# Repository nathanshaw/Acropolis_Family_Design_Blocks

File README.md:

# hsw_design_blocks
A collection of all the Hyper-Soundwalk EAGLE CAD design blocks.

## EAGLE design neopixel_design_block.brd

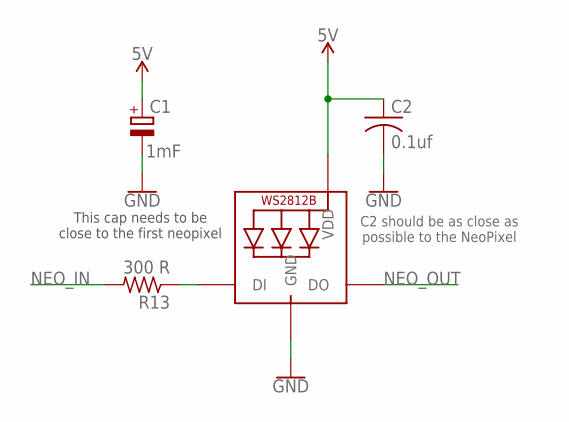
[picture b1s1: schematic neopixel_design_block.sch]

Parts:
C1: 1mF; 153CLV-1010
C2: 0.1uf; C0805K
NEO1: WS2812B5050; WS2812B
R13: 300 R; R0805

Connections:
5V: C1.+, C2.1, NEO1.1-VDD (VDD)
GND: C1.-, C2.2, NEO1.3-GND (GND)
NEO_IN: R13.2
NEO_OUT: NEO1.2-DOUT (DO)
NEO_P_CTRL_INT: NEO1.4-DIN (DI), R13.1

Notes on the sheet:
This cap needs to be close to the first neopixel
C2 should be as close as possible to the NeoPixel

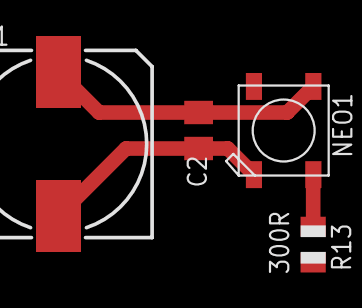
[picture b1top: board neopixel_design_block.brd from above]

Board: 2 copper layers, 4 parts (0 on the bottom side), 3 nets.

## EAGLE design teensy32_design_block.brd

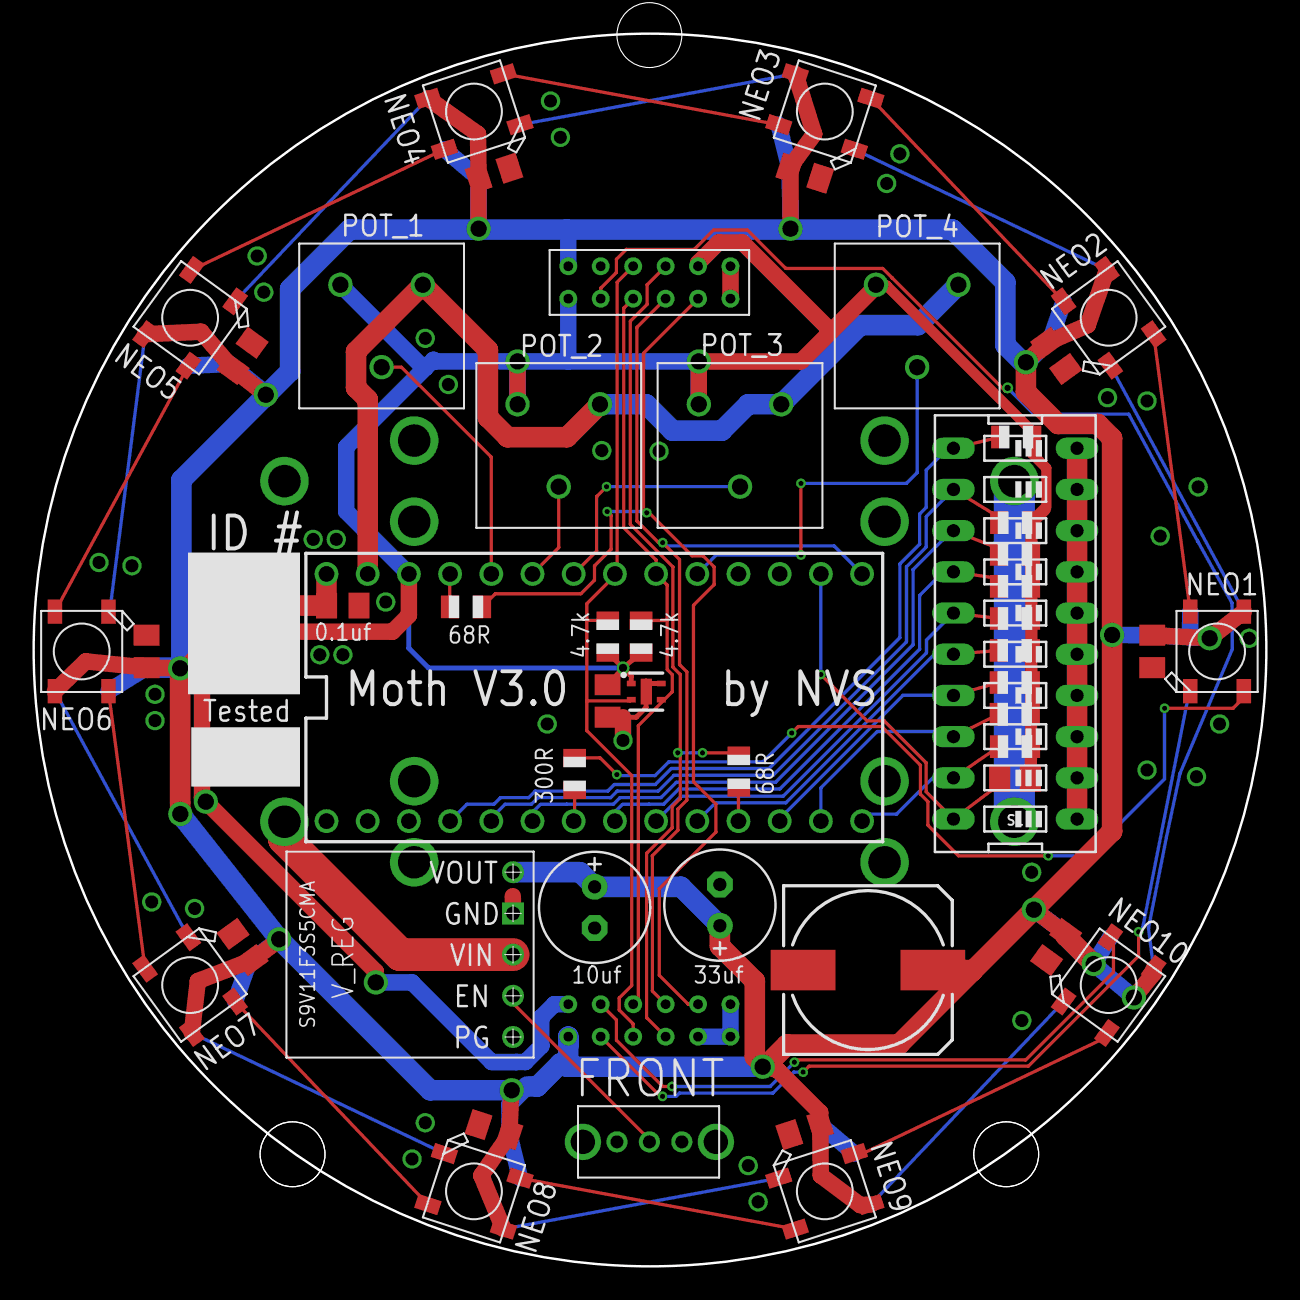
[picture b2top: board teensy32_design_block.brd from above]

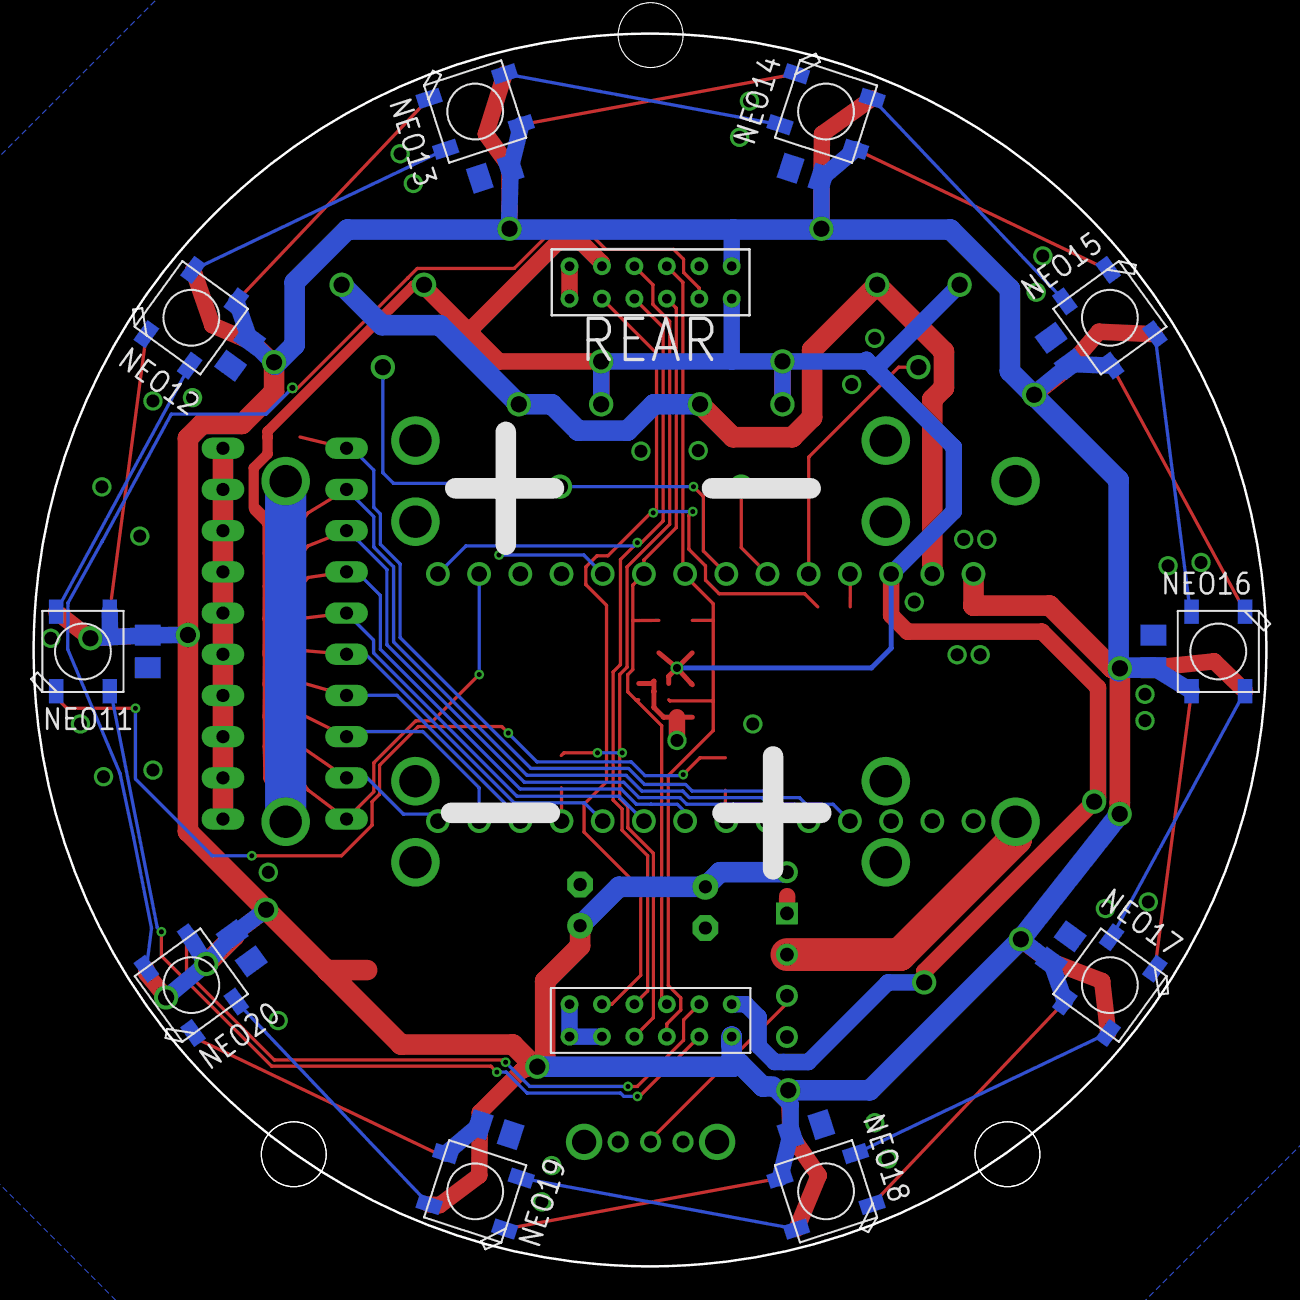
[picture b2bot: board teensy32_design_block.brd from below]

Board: 2 copper layers, 76.0 x 76.0 mm, 72 parts (22 on the bottom side), 51 nets.

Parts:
C10: 1mF; 153CLV-1010
FRONT: SAMTEC_ESQT_2X6_THROUGH_HOLE
NC1, NC2, NC3, NC4, NC5, NC6, NC7, NC8, NC9, NC10, NC11, NC12, NC13, NC14, NC15, NC16, NC17, NC18, NC19, NC20, NC21, NC24: 0.1uf; C0805K
NC22: 10uf; E2,5-7
NC23: 33uf; E2,5-7
NEO1, NEO2, NEO3, NEO4, NEO5, NEO6, NEO7, NEO8, NEO9, NEO10, NEO11, NEO12, NEO13, NEO14, NEO15, NEO16, NEO17, NEO18, NEO19, NEO20: WS2812B5050; WS2812B
POT1, POT2, POT3, POT4: 3386F_BOURNES_TRIM_POT; 3386_BOURNS_TRIM_POT
R1: 4.7k; R0805
R2: 4.7l; R0805
R3, R10: 68R; R0805
R13: 300 R; R0805
R14, R16, R17, R18, R19, R20, R21, R22, R24: 10k; R0805
R23: 10k; M0805
REAR: SAMTEC_ESQT_2X6_THROUGH_HOLE
S1: EDG-10
U1: SHTC3
U$1: 18500_CLIP_HOLDER; 3PINBATTERY_CLIP
U$2: OS_SPDT_SWITCH; OS_SPDT_SLIDE_SWITCH
U$3: TEENSY_3.1-3.2_DIL; TEENSY_3.0-3.2&LC_DIL
V_REG: S9V11F5S6CMA_NO_SEL; S9V11F3S5CMA_NO_SEL

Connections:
3.3V: FRONT.ESQT_6, NC24.1, POT1.P$2, POT2.P$2, POT3.P$2, POT4.P$2, R1.1, R2.1, R14.2, R16.2, R17.2, R18.2, R19.2, R20.2, R21.2, R22.2, R23.2, R24.2, REAR.ESQT_0, REAR.ESQT_7, U1.1, U$3.3.3V
5V: C10.+, FRONT.ESQT_5, NC1.1, NC2.1, NC3.1, NC4.1, NC5.1, NC6.1, NC7.1, NC8.1, NC9.1, NC10.1, NC11.1, NC12.1, NC13.1, NC14.1, NC15.1, NC16.1, NC17.1, NC18.1, NC19.1, NC20.1, NC21.1, NC22.+, NC23.+, NEO1.1-VDD, NEO2.1-VDD, NEO3.1-VDD, NEO4.1-VDD, NEO5.1-VDD, NEO6.1-VDD, NEO7.1-VDD, NEO8.1-VDD, NEO9.1-VDD, NEO10.1-VDD, NEO11.1-VDD, NEO12.1-VDD, NEO13.1-VDD, NEO14.1-VDD, NEO15.1-VDD, NEO16.1-VDD, NEO17.1-VDD, NEO18.1-VDD, NEO19.1-VDD, NEO20.1-VDD, REAR.ESQT_11, U$3.VIN, V_REG.VOUT
AGND: POT1.P$3, POT2.P$3, POT3.P$3, POT4.P$3, U$3.AGND
BCLK: FRONT.ESQT_2, R3.2, REAR.ESQT_8
BCLK88: R3.1, U$3.9
BRIDGE1: FRONT.ESQT_7, NEO10.2-DOUT
BRIDGE2: NEO20.2-DOUT, REAR.ESQT_1
GND: C10.-, FRONT.ESQT_0, FRONT.ESQT_1, FRONT.ESQT_11, NC1.2, NC2.2, NC3.2, NC4.2, NC5.2, NC6.2, NC7.2, NC8.2, NC9.2, NC10.2, NC11.2, NC12.2, NC13.2, NC14.2, NC15.2, NC16.2, NC17.2, NC18.2, NC19.2, NC20.2, NC21.2, NC22.-, NC23.-, NC24.2, NEO1.3-GND, NEO2.3-GND, NEO3.3-GND, NEO4.3-GND, NEO5.3-GND, NEO6.3-GND, NEO7.3-GND, NEO8.3-GND, NEO9.3-GND, NEO10.3-GND, NEO11.3-GND, NEO12.3-GND, NEO13.3-GND, NEO14.3-GND, NEO15.3-GND, NEO16.3-GND, NEO17.3-GND, NEO18.3-GND, NEO19.3-GND, NEO20.3-GND, REAR.ESQT_5, REAR.ESQT_6, S1.1, S1.2, S1.3, S1.4, S1.5, S1.6, S1.7, S1.8, S1.9, S1.10, U1.4, U1.5, U$1.P$7, U$2.P$2, U$3.GND, V_REG.GND
LRCLK: FRONT.ESQT_10, R10.2, REAR.ESQT_4
LRCLK88: R10.1, U$3.23/A9
M0: R23.1, S1.20, U$3.14/A0
M1: R22.1, S1.19, U$3.12
M2: R21.1, S1.18, U$3.11
M3: R20.1, S1.17, U$3.10
M4: R19.1, S1.16, U$3.8
M5: R18.1, S1.15, U$3.7
M6: R17.1, S1.14, U$3.6
M7: R16.1, S1.13, U$3.4
M8: R14.1, S1.12, U$3.3
M9: R24.1, S1.11, U$3.2
MIC_DATA: FRONT.ESQT_9, REAR.ESQT_3, U$3.13
unnamed: U$1.P$6, U$1.P$12
unnamed: U$1.P$1, V_REG.VIN
unnamed: NEO2.2-DOUT, NEO3.4-DIN
unnamed: NEO5.2-DOUT, NEO6.4-DIN
unnamed: NEO9.2-DOUT, NEO10.4-DIN
unnamed: NEO11.2-DOUT, NEO12.4-DIN
unnamed: NEO4.2-DOUT, NEO5.4-DIN
unnamed: NEO15.2-DOUT, NEO16.4-DIN
unnamed: NEO3.2-DOUT, NEO4.4-DIN
unnamed: NEO7.2-DOUT, NEO8.4-DIN
unnamed: NEO8.2-DOUT, NEO9.4-DIN
unnamed: NEO18.2-DOUT, NEO19.4-DIN
unnamed: NEO13.2-DOUT, NEO14.4-DIN
unnamed: NEO16.2-DOUT, NEO17.4-DIN
unnamed: NEO12.2-DOUT, NEO13.4-DIN
unnamed: NEO19.2-DOUT, NEO20.4-DIN
unnamed: NEO6.2-DOUT, NEO7.4-DIN
unnamed: NEO17.2-DOUT, NEO18.4-DIN
NEOLOOP: FRONT.ESQT_4, NEO11.4-DIN
NEO_P1: NEO1.2-DOUT, NEO2.4-DIN
NEO_P2: NEO14.2-DOUT, NEO15.4-DIN
NEO_P_CTRL: R13.2, U$3.5
NEO_P_CTRL_INT: NEO1.4-DIN, R13.1
POT1: POT1.P$1, U$3.22/A8
POT2: POT2.P$1, U$3.21/A7
POT3: POT3.P$1, U$3.20/A6
POT4: POT4.P$1, U$3.17/A3
SCL: FRONT.ESQT_3, R2.2, REAR.ESQT_9, U1.2, U$3.19/A5
SDA: FRONT.ESQT_8, R1.2, REAR.ESQT_2, U1.3, U$3.18/A4
SHDN: U$2.P$1, V_REG.EN

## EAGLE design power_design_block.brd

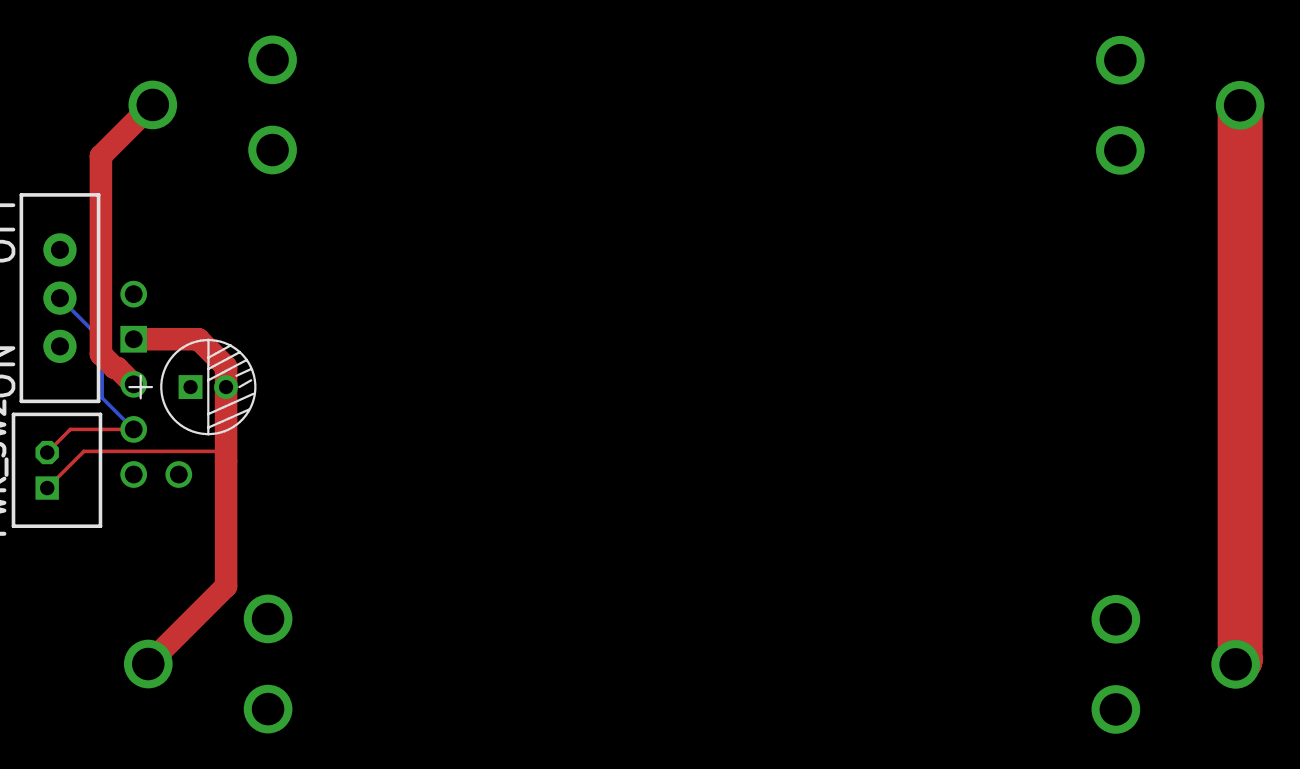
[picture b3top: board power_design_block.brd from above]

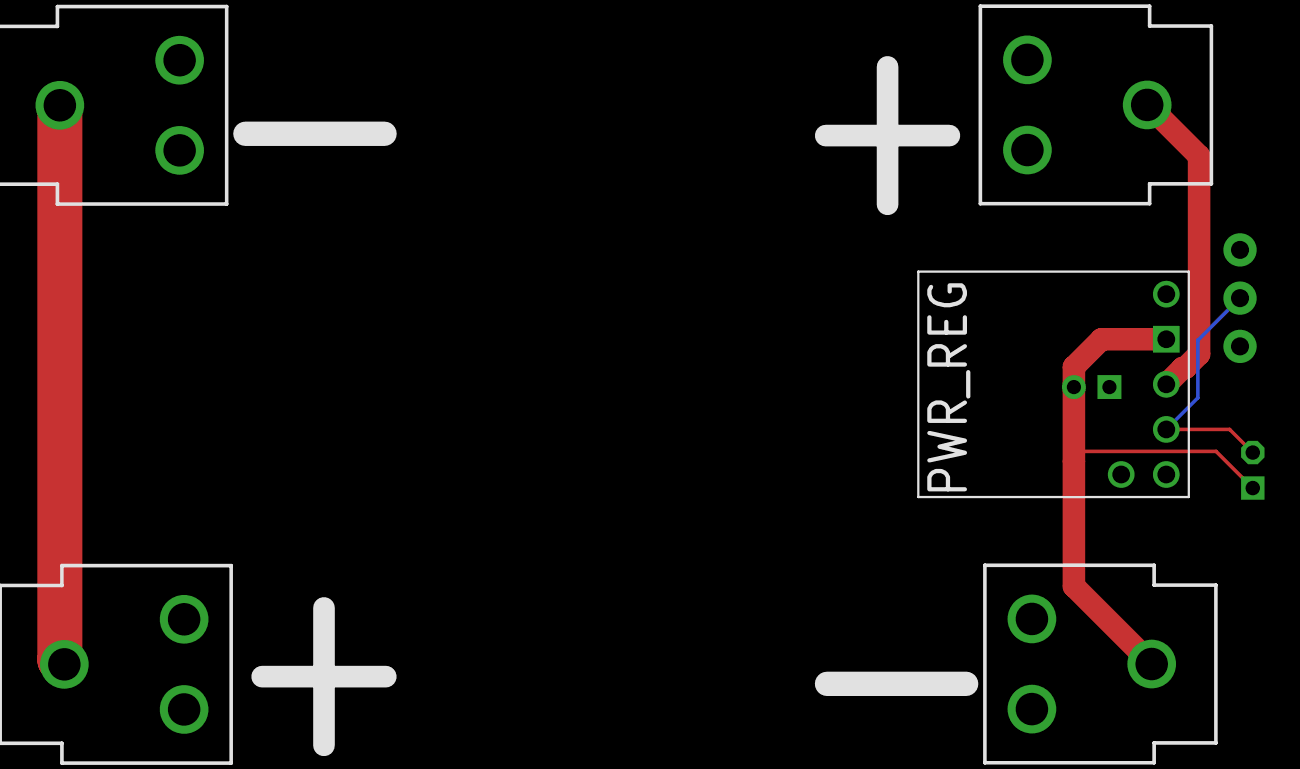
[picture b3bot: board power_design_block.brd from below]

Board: 2 copper layers, 6 parts (3 on the bottom side), 4 nets.

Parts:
BT1, BT2: BATTERY_18650-HOLDER
C1: 33uf; PC-D5.3MM
PWR_REG: S9V11F5S6CMA; S9V11F3S5CMA_BETTER_PINS
PWR_SW1: SWITCH_SPDT_PTH_11.6X4.0MM_LOCK
PWR_SW2: JST-PH; B2B-PH-K

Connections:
unnamed: BT2.GND@1, C1.-, PWR_REG.GND, PWR_SW1.1, PWR_SW2.1
unnamed: PWR_REG.EN, PWR_SW1.2, PWR_SW2.2
unnamed: BT1.GND@1, BT2.PWR@1
VIN: BT1.PWR@1, C1.+, PWR_REG.VIN

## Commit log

2020-09-09 updated the gitignore and addded all of the current design blocks
2020-09-09 updated gitignore to ignore the backup and history files for the design blocks
2020-09-10 updated neopixels, teensy32 and veml design blocks
2020-09-15 lots up updates to most blocks, getting ready for the first draft of Chapter 3
2020-09-16 updated upser_controls_switches design block
2022-09-17 first real commit

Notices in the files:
parts and their libraries:
SparkFun-PowerSymbols: Licensing: Creative Commons ShareAlike 4.0 International - https://creativecommons.org/licenses/by-sa/4.0
con-jst-ph: Copyright (C) 2016, Bob Starr
